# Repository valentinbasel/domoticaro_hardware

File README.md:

# domoticaro_hardware
diseño del PCB de placas basadas en pinguino, para trabajo con domotica en las escuelas

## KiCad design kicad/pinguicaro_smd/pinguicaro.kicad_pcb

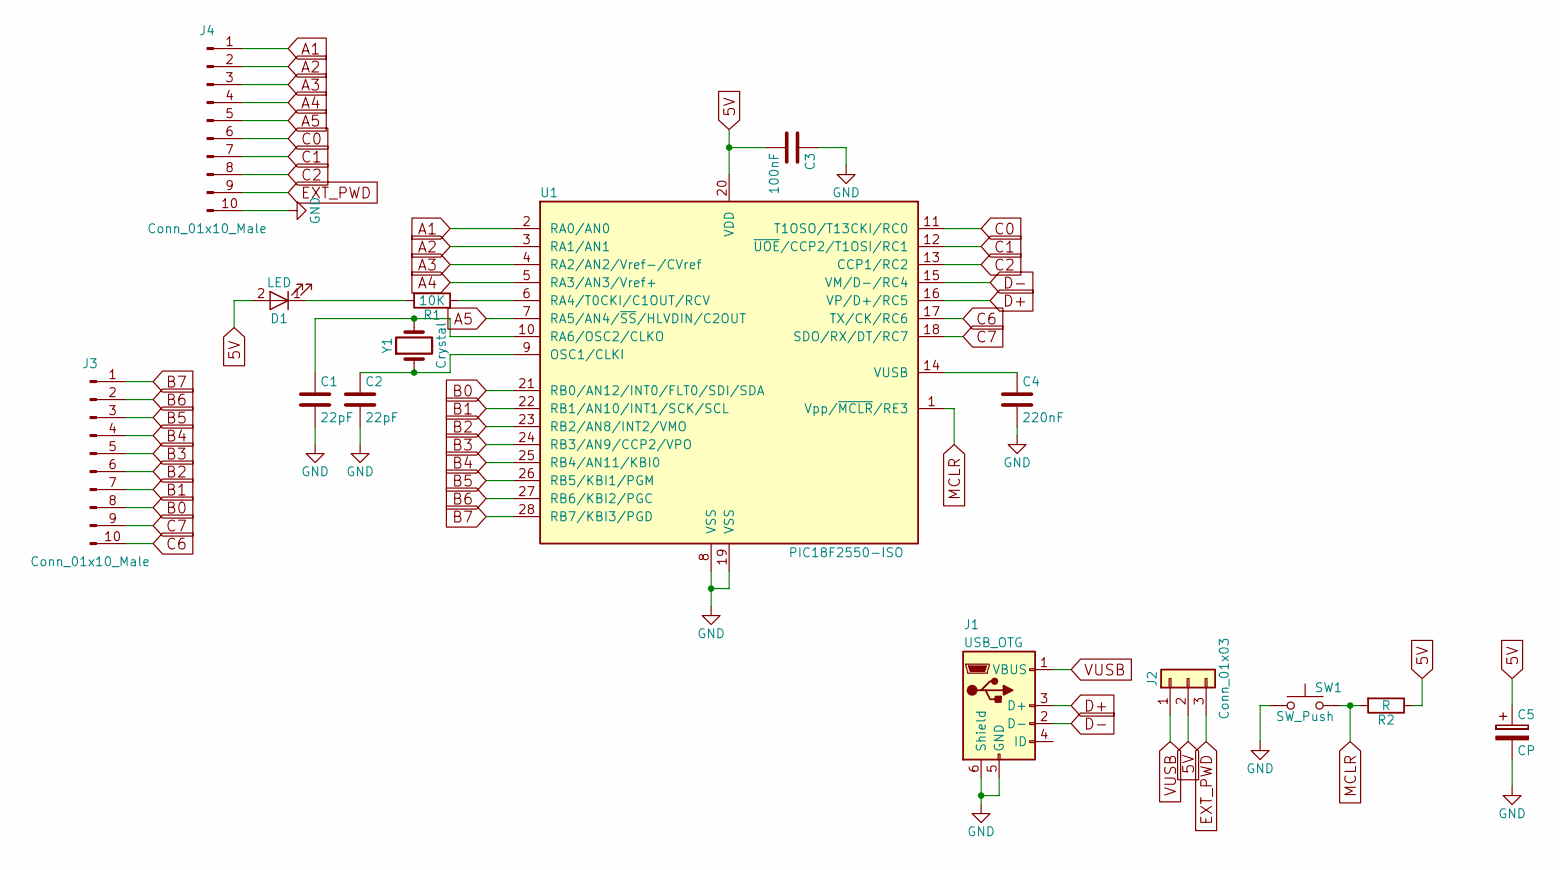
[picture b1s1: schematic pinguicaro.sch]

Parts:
C1, C2: 22pF; C_0805
C3: 100nF; C_0805
C4: 220nF; C_0805
C5: CP; CP_Elec_6.3x5.3
D1: LED; LED_0805
J1: USB_OTG; USB_Mini-B
J2: Conn_01x03; Pin_Header_Straight_1x03_Pitch2.54mm
J3, J4: Conn_01x10_Male; Pin_Header_Straight_1x10_Pitch2.54mm
R1: 10K; R_0805
R2: R; R_0805
SW1: SW_Push; SW_SPST_B3SL-1022P
U1: PIC18F2550-ISO; SOIC-28W_7.5x17.9mm_Pitch1.27mm
Y1: Crystal; Crystal_SMD_HC49-SD

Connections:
5V: C3.2, C5.1, D1.2 (A), J2.2, R2.1, U1.20 (VDD)
A1: J4.1, U1.2 (RA0/AN0)
A2: J4.2, U1.3 (RA1/AN1)
A3: J4.3, U1.4 (RA2/AN2/Vref-/CVref)
A4: J4.4, U1.5 (RA3/AN3/Vref+)
A5: J4.5, U1.7 (RA5/AN4/~SS~/HLVDIN/C2OUT)
B0: J3.8, U1.21 (RB0/AN12/INT0/FLT0/SDI/SDA)
B1: J3.7, U1.22 (RB1/AN10/INT1/SCK/SCL)
B2: J3.6, U1.23 (RB2/AN8/INT2/VMO)
B3: J3.5, U1.24 (RB3/AN9/CCP2/VPO)
B4: J3.4, U1.25 (RB4/AN11/KBI0)
B5: J3.3, U1.26 (RB5/KBI1/PGM)
B6: J3.2, U1.27 (RB6/KBI2/PGC)
B7: J3.1, U1.28 (RB7/KBI3/PGD)
C0: J4.6, U1.11 (T1OSO/T13CKI/RC0)
C1: J4.7, U1.12 (~UOE~/CCP2/T1OSI/RC1)
C2: J4.8, U1.13 (CCP1/RC2)
C6: J3.10, U1.17 (TX/CK/RC6)
C7: J3.9, U1.18 (SDO/RX/DT/RC7)
D+: J1.3 (D+), U1.16 (VP/D+/RC5)
D-: J1.2 (D-), U1.15 (VM/D-/RC4)
EXT_PWD: J2.3, J4.9
GND: C1.2, C2.2, C3.1, C4.2, C5.2, J1.5 (GND), J1.6 (Shield), J4.10, SW1.1, U1.8 (VSS), U1.19 (VSS)
MCLR: R2.2, SW1.2, U1.1 (Vpp/~MCLR~/RE3)
unnamed: C1.1, U1.10 (RA6/OSC2/CLKO), Y1.2
unnamed: C2.1, U1.9 (OSC1/CLKI), Y1.1
unnamed: C4.1, U1.14 (VUSB)
unnamed: D1.1 (K), R1.2
unnamed: R1.1, U1.6 (RA4/T0CKI/C1OUT/RCV)
VUSB: J1.1 (VBUS), J2.1

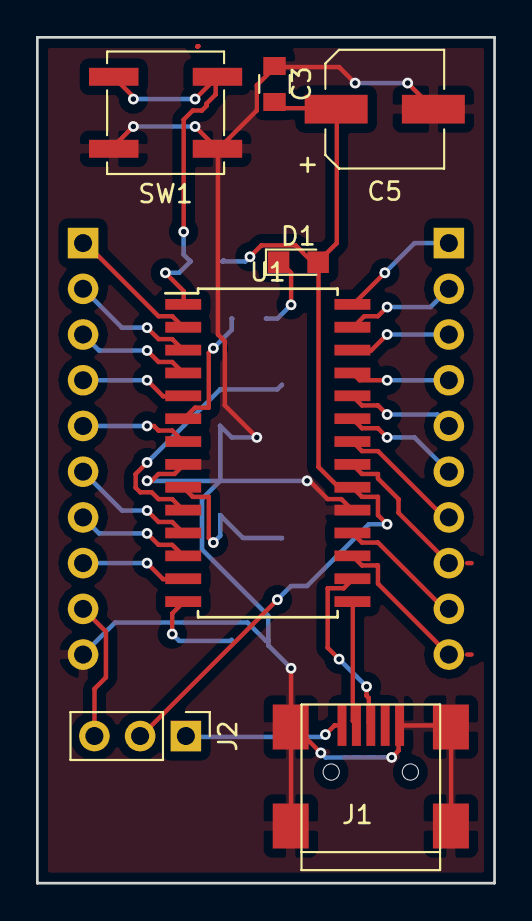
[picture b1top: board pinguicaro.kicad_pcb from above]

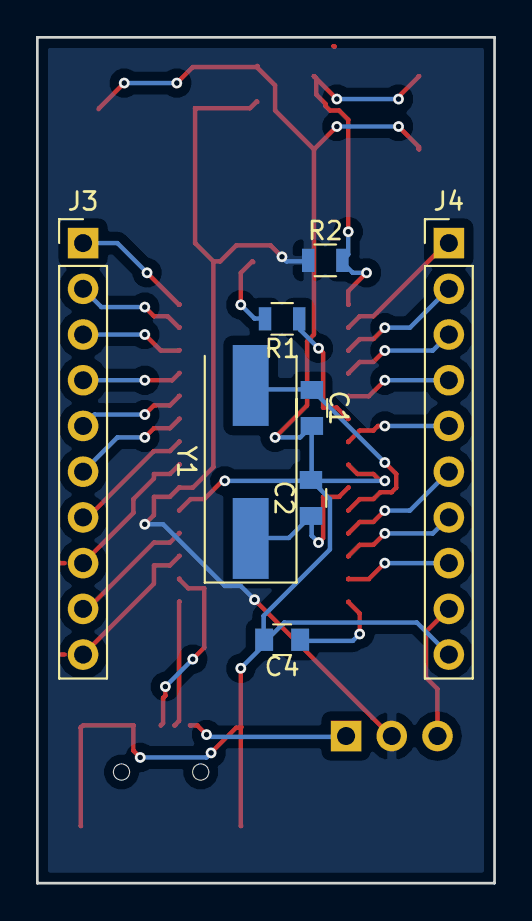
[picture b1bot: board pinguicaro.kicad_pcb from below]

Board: 2 copper layers, 25.4 x 47.0 mm, 15 parts (8 on the bottom side), 30 nets.

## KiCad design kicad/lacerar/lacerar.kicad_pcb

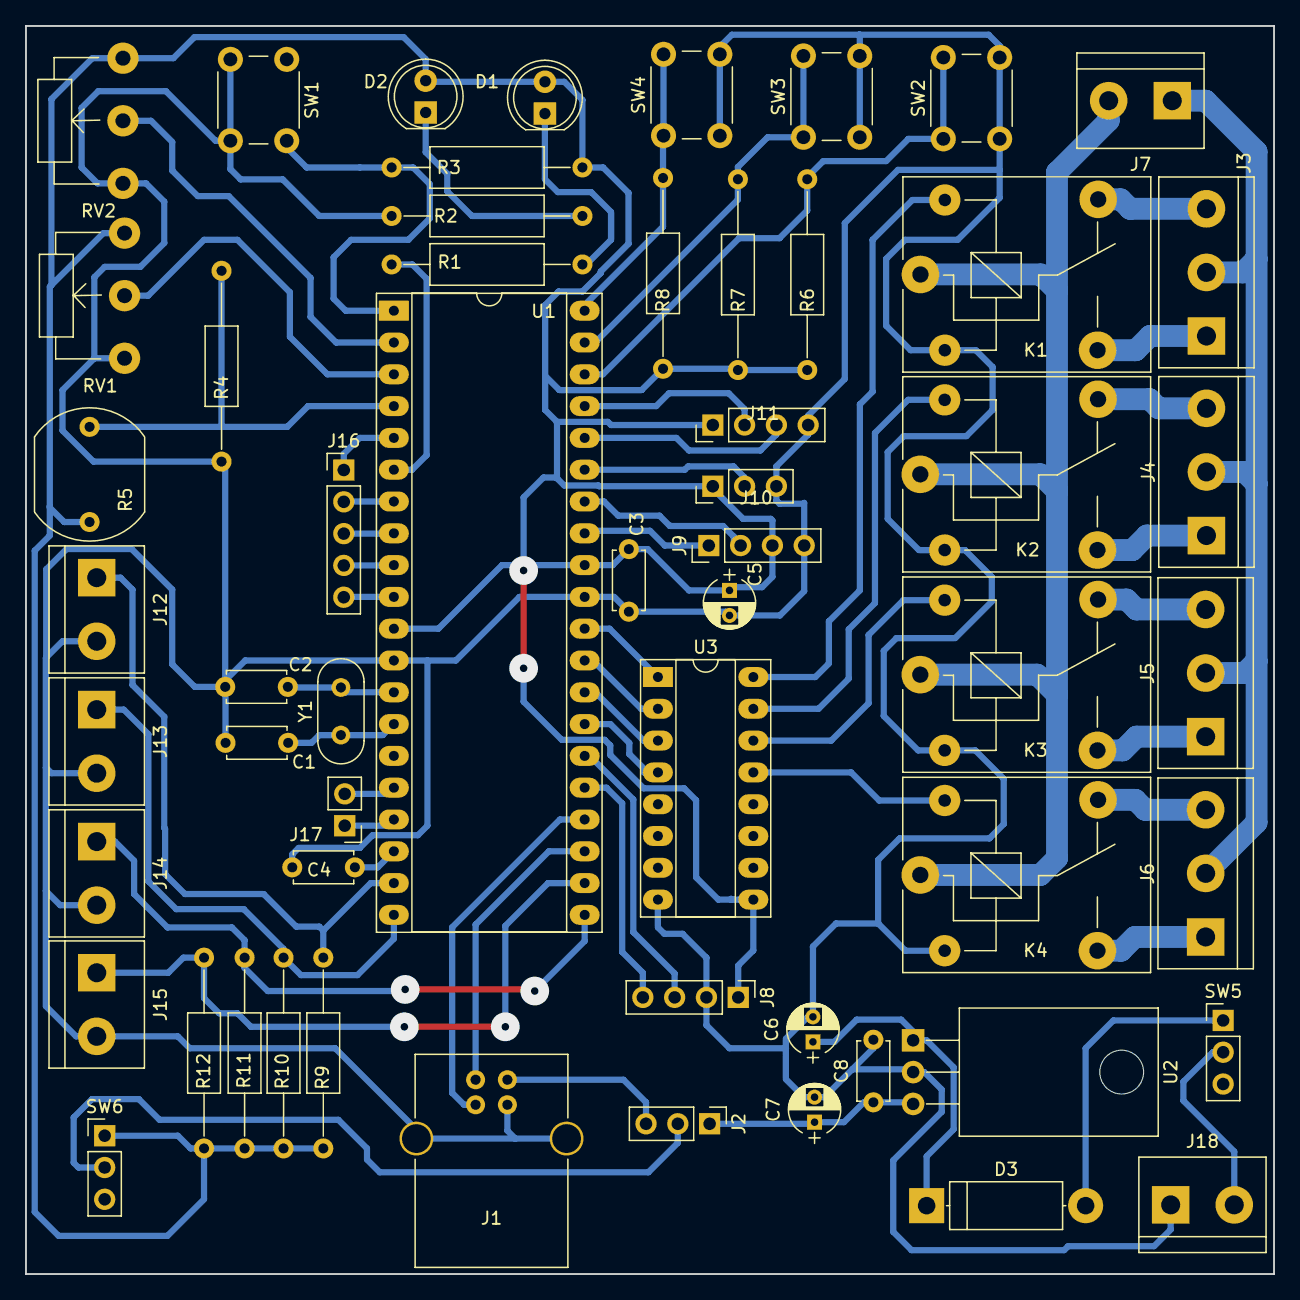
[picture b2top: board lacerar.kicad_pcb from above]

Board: 2 copper layers, 99.7 x 99.7 mm, 57 parts (0 on the bottom side), 59 nets.

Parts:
C1, C2: 22PF; C_Disc_D4.7mm_W2.5mm_P5.00mm
C3: 100NF; C_Disc_D4.7mm_W2.5mm_P5.00mm
C4: 220NF; C_Disc_D4.7mm_W2.5mm_P5.00mm
C5: 100UF; CP_Radial_D4.0mm_P2.00mm
C6, C7: 100uF; CP_Radial_D4.0mm_P2.00mm
C8: 0.1uF; C_Disc_D4.7mm_W2.5mm_P5.00mm
D1: RUN_LED; LED_D5.0mm
D2: POWER_LED; LED_D5.0mm
D3: 1N4007; D_5W_P12.70mm_Horizontal
J1: USB_B
J2: SELECT_VOLT; Pin_Header_Straight_1x03_Pitch2.54mm
J3, J4, J5, J6: NC - COM - NA; bornier3
J7, J18: + / -; bornier2
J8: HC_05/06; Pin_Header_Straight_1x04_Pitch2.54mm
J9: I2C; Pin_Header_Straight_1x04_Pitch2.54mm
J10: DTH_12; Pin_Header_Straight_1x03_Pitch2.54mm
J11: HC-SR04; Pin_Header_Straight_1x04_Pitch2.54mm
J12: sens_dig1; bornier2
J13: sens_dig2; bornier2
J14: sens_dig3; bornier2
J15: sens_dig4; bornier2
J16: sensores_analogicos; Pin_Header_Straight_1x05_Pitch2.54mm
J17: PWM; Pin_Header_Straight_1x02_Pitch2.54mm
K1: RELE1; Relay_SPDT_SANYOU_SRD_Series_Form_C
K2: RELE2; Relay_SPDT_SANYOU_SRD_Series_Form_C
K3: RELE3; Relay_SPDT_SANYOU_SRD_Series_Form_C
K4: RELE4; Relay_SPDT_SANYOU_SRD_Series_Form_C
R1, R2: 470; R_Axial_DIN0309_L9.0mm_D3.2mm_P15.24mm_Horizontal
R3: 10k; R_Axial_DIN0309_L9.0mm_D3.2mm_P15.24mm_Horizontal
R4, R6, R7, R8, R9, R10, R11, R12: 1K; R_Axial_DIN0207_L6.3mm_D2.5mm_P15.24mm_Horizontal
R5: LDR03; Resistor_LDR_10x8.5_RM7.6
RV1: POT_01; Potentiometer_WirePads_largePads
RV2: POT_02; Potentiometer_WirePads_largePads
SW1: RESET; SW_PUSH_6mm
SW2: boton1; SW_PUSH_6mm
SW3: boton2; SW_PUSH_6mm
SW4: boton3; SW_PUSH_6mm
SW5, SW6: ON/OFF; Pin_Header_Straight_1x03_Pitch2.54mm
U1: PIC18F4550-IP; DIP-40_W15.24mm_Socket_LongPads
U2: L7805; TO-220_Horizontal
U3: ULN2003; DIP-16_W7.62mm_Socket_LongPads
Y1: 20MHZ; Crystal_HC52-8mm_Vertical

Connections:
+5V: C3.2, C5.1, D1.2, D2.2, J8.1, J9.3, J10.1, J11.1, R3.2, R5.1, R6.2, R7.2, R8.2, R9.2, R10.2, R11.2, R12.2, RV1.3, RV2.3, SW6.1, U1.11, U1.32, U3.9
COMUN: J7.2, K1.1, K2.1, K3.1, K4.1
FUENT5V: C7.1, C8.1, J2.1, U2.3
GND: C1.2, C2.2, C3.1, C4.1, C5.2, C6.2, C7.2, C8.2, J1.4, J1.5, J8.2, J9.4, J10.3, J11.4, J12.2, J13.2, J14.2, J15.2, J18.1, K1.2, K2.2, K3.2, K4.2, R2.1, R4.2, RV1.1, RV2.1, SW1.2, SW2.2, SW3.2, SW4.2, U1.12, U1.31, U2.2, U3.8
unnamed: C1.1, U1.14, Y1.1
unnamed: C2.1, U1.13, Y1.2
unnamed: C4.2, U1.18
unnamed: C6.1, D3.1, U2.1
unnamed: D1.1, R1.1
unnamed: D2.1, R2.2
unnamed: D3.2, SW5.1
unnamed: J1.2, U1.23
unnamed: J1.3, U1.24
unnamed: J2.2, SW6.2
unnamed: J3.1, K1.3
unnamed: J3.3, K1.4
unnamed: J4.1, K2.3
unnamed: J4.3, K2.4
unnamed: J5.1, K3.3
unnamed: J5.3, K3.4
unnamed: J6.1, K4.3
unnamed: J6.3, K4.4
unnamed: J18.2, SW5.2
unnamed: R1.2, U1.6
unnamed: R3.1, SW1.1, U1.1
P1: K1.5, U3.16
P2: K2.5, U3.15
P3: K3.5, U3.14
P4: K4.5, U3.13
RA0: RV2.2, U1.2
RA1: RV1.2, U1.3
RA2: R4.1, R5.2, U1.4
RA3: J16.1, U1.5
RA5: J16.2, U1.7
RB0_SDA: J9.1, U1.33
RB1_SCK: J9.2, U1.34
RB2: J10.2, U1.35
RB3: J11.3, U1.36
RB4: J11.2, U1.37
RB5: R6.1, SW2.1, U1.38
RB6: R7.1, SW3.1, U1.39
RB7: R8.1, SW4.1, U1.40
RC1_pwm1: J17.1, U1.17
RC1_pwm2: J17.2, U1.16
RC6_TX: J8.4, U1.25
RC7_RX: J8.3, U1.26
RD0: J12.1, R9.1, U1.19
RD1: J13.1, R10.1, U1.20
RD2: J14.1, R11.1, U1.21
RD3: J15.1, R12.1, U1.22
RD4: U1.27, U3.4
RD5: U1.28, U3.3
RD6: U1.29, U3.2
RD7: U1.30, U3.1
RE0: J16.3, U1.8
RE1: J16.4, U1.9
RE2: J16.5, U1.10
VBUS: J1.1, J2.3
VIVO: J3.2, J4.2, J5.2, J6.2, J7.1

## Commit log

2019-07-04 primer commit con el diseño de pcb de la placa
2019-09-16 creo placa smd de pic 18f2550
